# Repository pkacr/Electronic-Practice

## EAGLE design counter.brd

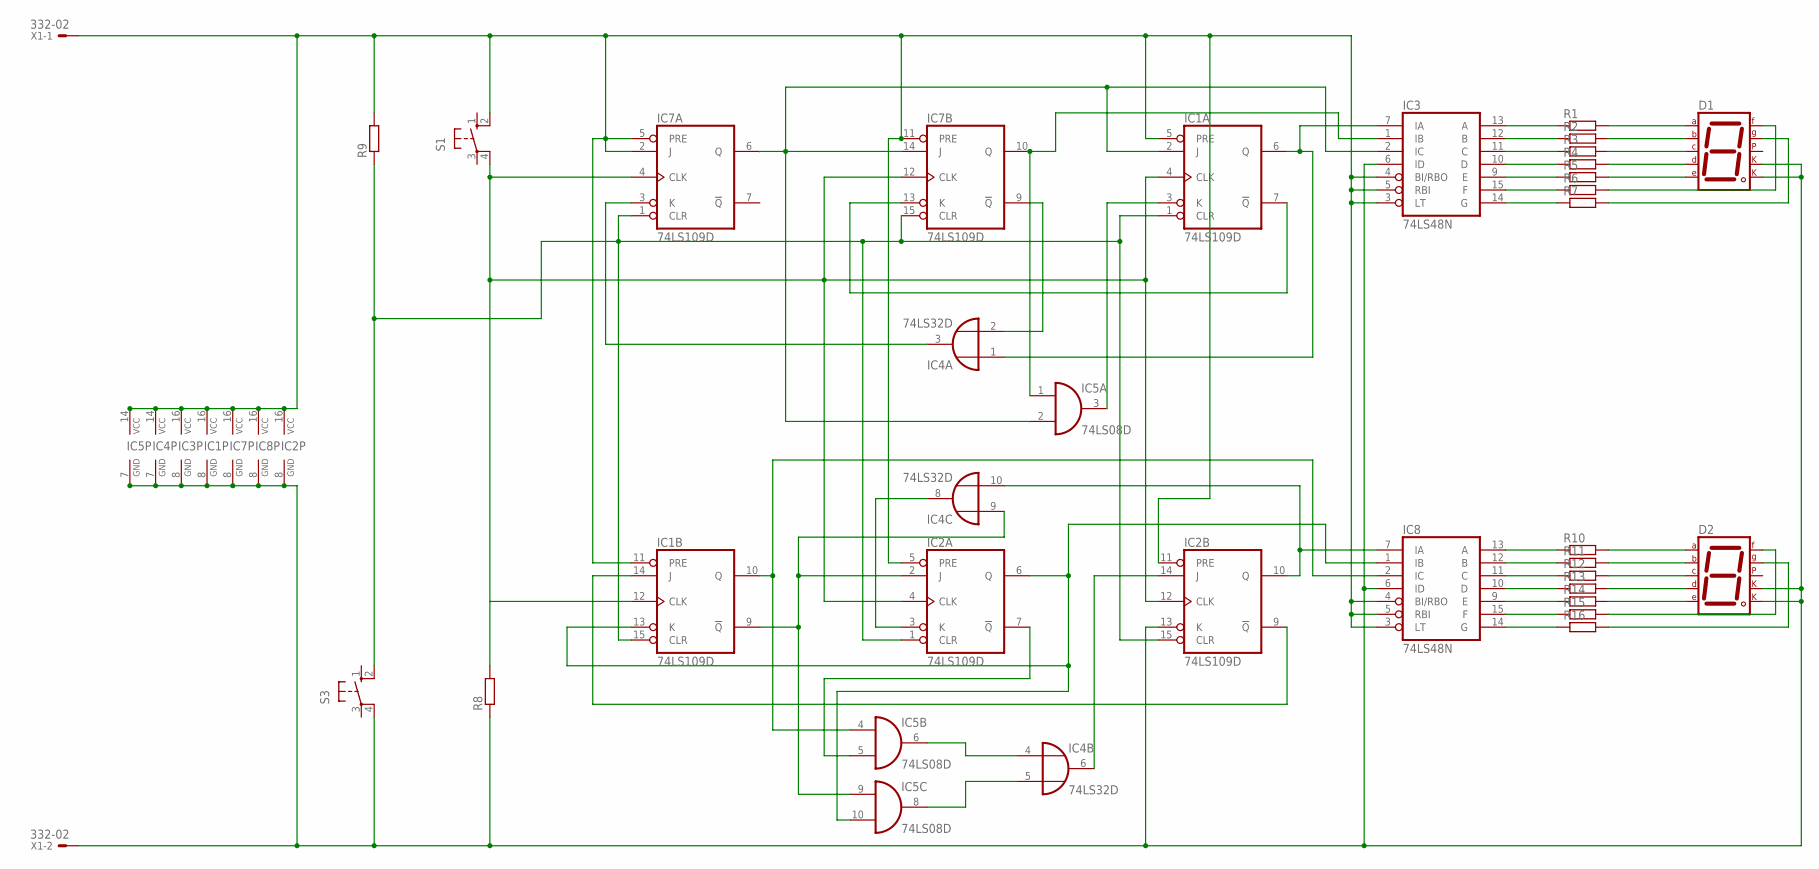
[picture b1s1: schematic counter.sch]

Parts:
D1, D2: 7SEG-CK; 7SEG-13
IC1, IC2, IC7: 74LS109D; SO16
IC3, IC8: 74LS48N; DIL16
IC4: 74LS32D; SO14
IC5: 74LS08D; SO14
R1, R2, R3, R4, R5, R6, R7, R8, R9, R10, R11, R12, R13, R14, R15, R16: R-EU_M0805; M0805
S1, S3: 10-XX; B3F-10XX
X1: 332-02

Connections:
unnamed: IC3.13 (A), R1.1
unnamed: D1.7 (A), R1.2
unnamed: IC3.12 (B), R2.1
unnamed: D1.6 (B), R2.2
unnamed: IC3.11 (C), R3.1
unnamed: D1.4 (C), R3.2
unnamed: IC3.10 (D), R4.1
unnamed: D1.2 (D), R4.2
unnamed: IC3.9 (E), R5.1
unnamed: D1.1 (E), R5.2
unnamed: IC3.15 (F), R6.1
unnamed: D1.9 (F), R6.2
unnamed: IC3.14 (G), R7.1
unnamed: D1.10 (G), R7.2
unnamed: IC1.4 (CLK), IC1.12 (CLK), IC2.4 (CLK), IC2.12 (CLK), IC7.4 (CLK), IC7.12 (CLK), R8.2, S1.4 (P1)
unnamed: IC1.2 (J), IC3.2 (IC), IC5.2 (I1), IC7.6 (Q), IC7.14 (J)
unnamed: IC1.1 (CLR), IC1.15 (CLR), IC2.1 (CLR), IC2.15 (CLR), IC7.1 (CLR), IC7.15 (CLR), R9.1, S3.2 (S1)
unnamed: IC4.3 (O), IC7.3 (K)
unnamed: IC1.7 (!Q), IC7.13 (K)
unnamed: IC3.1 (IB), IC5.1 (I0), IC7.10 (Q)
unnamed: IC2.10 (Q), IC4.10 (I1), IC8.7 (IA)
unnamed: IC1.3 (K), IC5.3 (O)
unnamed: IC1.14 (J), IC2.9 (!Q)
unnamed: IC4.2 (I1), IC7.9 (!Q)
unnamed: IC1.9 (!Q), IC2.2 (J), IC4.9 (I0), IC5.9 (I0)
unnamed: IC1.6 (Q), IC3.7 (IA), IC4.1 (I0)
unnamed: IC8.13 (A), R10.1
unnamed: IC2.14 (J), IC4.6 (O)
unnamed: D2.7 (A), R10.2
unnamed: IC8.12 (B), R11.1
unnamed: D2.6 (B), R11.2
unnamed: IC8.11 (C), R12.1
unnamed: D2.4 (C), R12.2
unnamed: IC8.10 (D), R13.1
unnamed: D2.2 (D), R13.2
unnamed: IC8.9 (E), R14.1
unnamed: D2.1 (E), R14.2
unnamed: IC8.15 (F), R15.1
unnamed: D2.9 (F), R15.2
unnamed: IC8.14 (G), R16.1
unnamed: D2.10 (G), R16.2
unnamed: IC1.5 (PRE), IC1.11 (PRE), IC1.16 (VCC), IC2.5 (PRE), IC2.11 (PRE), IC2.16 (VCC), IC3.3 (LT), IC3.4 (BI/RBO), IC3.5 (RBI), IC3.16 (VCC), IC4.14 (VCC), IC5.14 (VCC), IC7.2 (J), IC7.5 (PRE), IC7.11 (PRE), IC7.16 (VCC), IC8.3 (LT), IC8.4 (BI/RBO), IC8.5 (RBI), IC8.16 (VCC), R9.2, S1.2 (S1), X1.1
unnamed: D1.3 (CK1), D1.8 (CK2), D2.3 (CK1), D2.8 (CK2), IC1.8 (GND), IC2.8 (GND), IC2.13 (K), IC3.6 (ID), IC3.8 (GND), IC4.7 (GND), IC5.7 (GND), IC7.8 (GND), IC8.6 (ID), IC8.8 (GND), R8.1, S3.4 (P1), X1.2
unnamed: IC2.7 (!Q), IC5.5 (I1)
unnamed: IC4.4 (I0), IC5.6 (O)
unnamed: IC4.5 (I1), IC5.8 (O)
unnamed: IC1.10 (Q), IC5.4 (I0), IC8.2 (IC)
unnamed: IC2.3 (K), IC4.8 (O)
unnamed: IC1.13 (K), IC2.6 (Q), IC5.10 (I1), IC8.1 (IB)

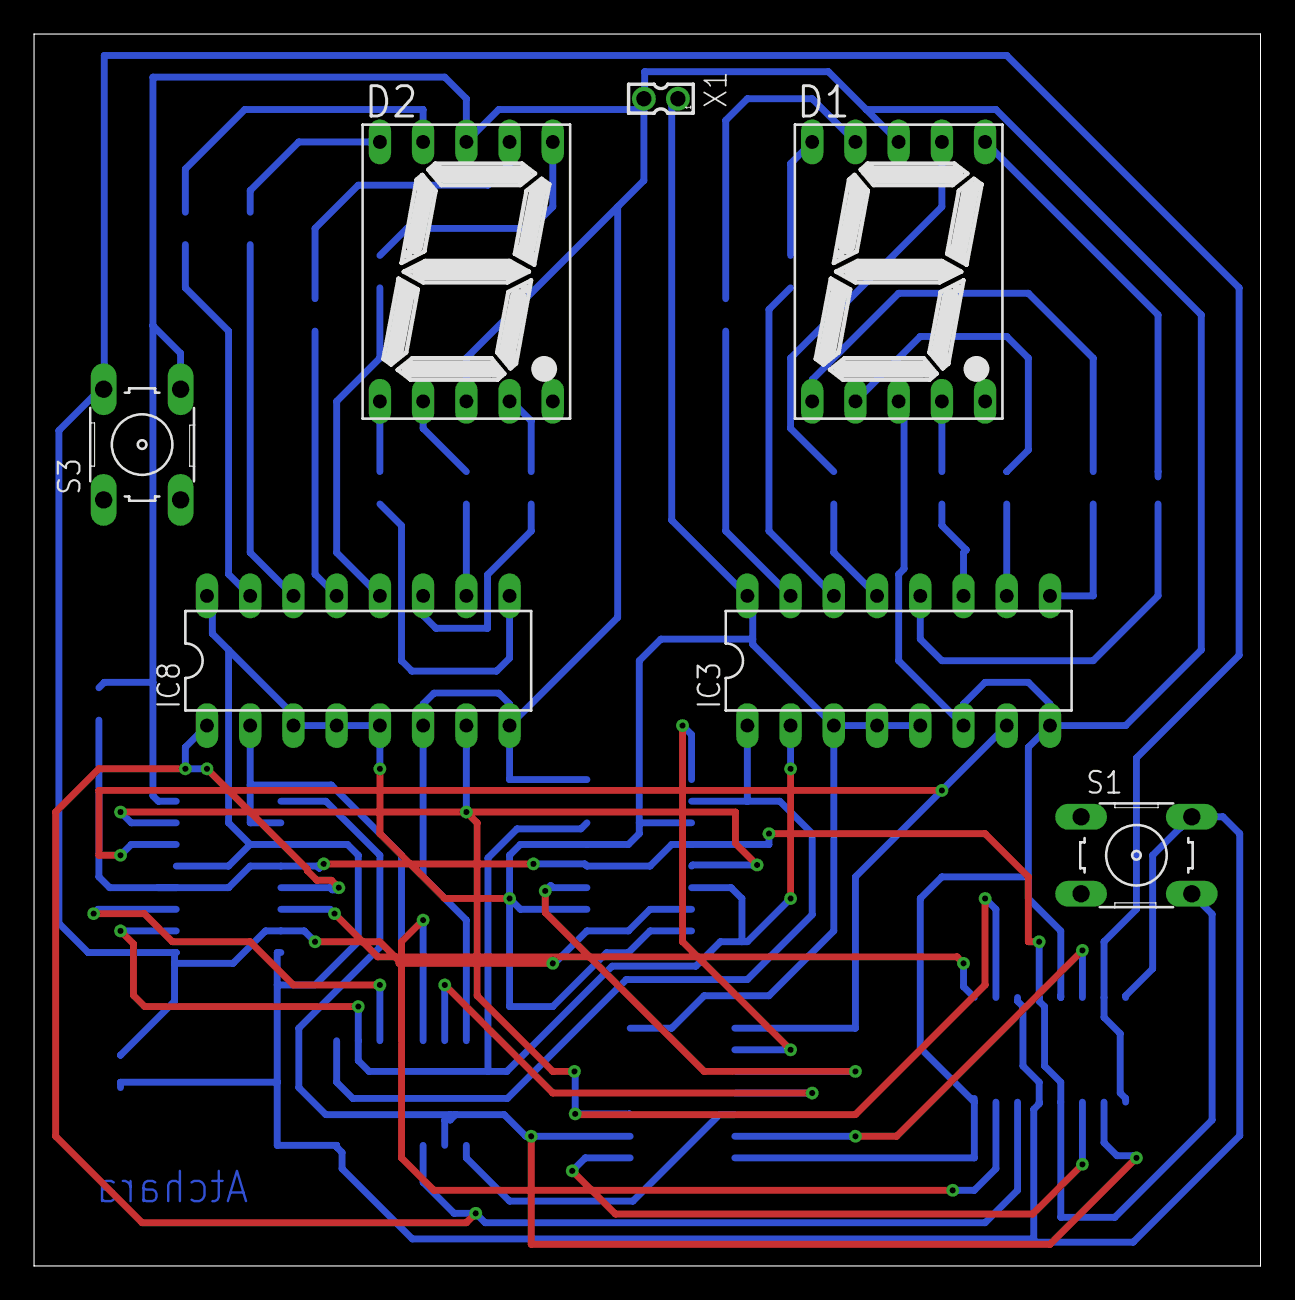
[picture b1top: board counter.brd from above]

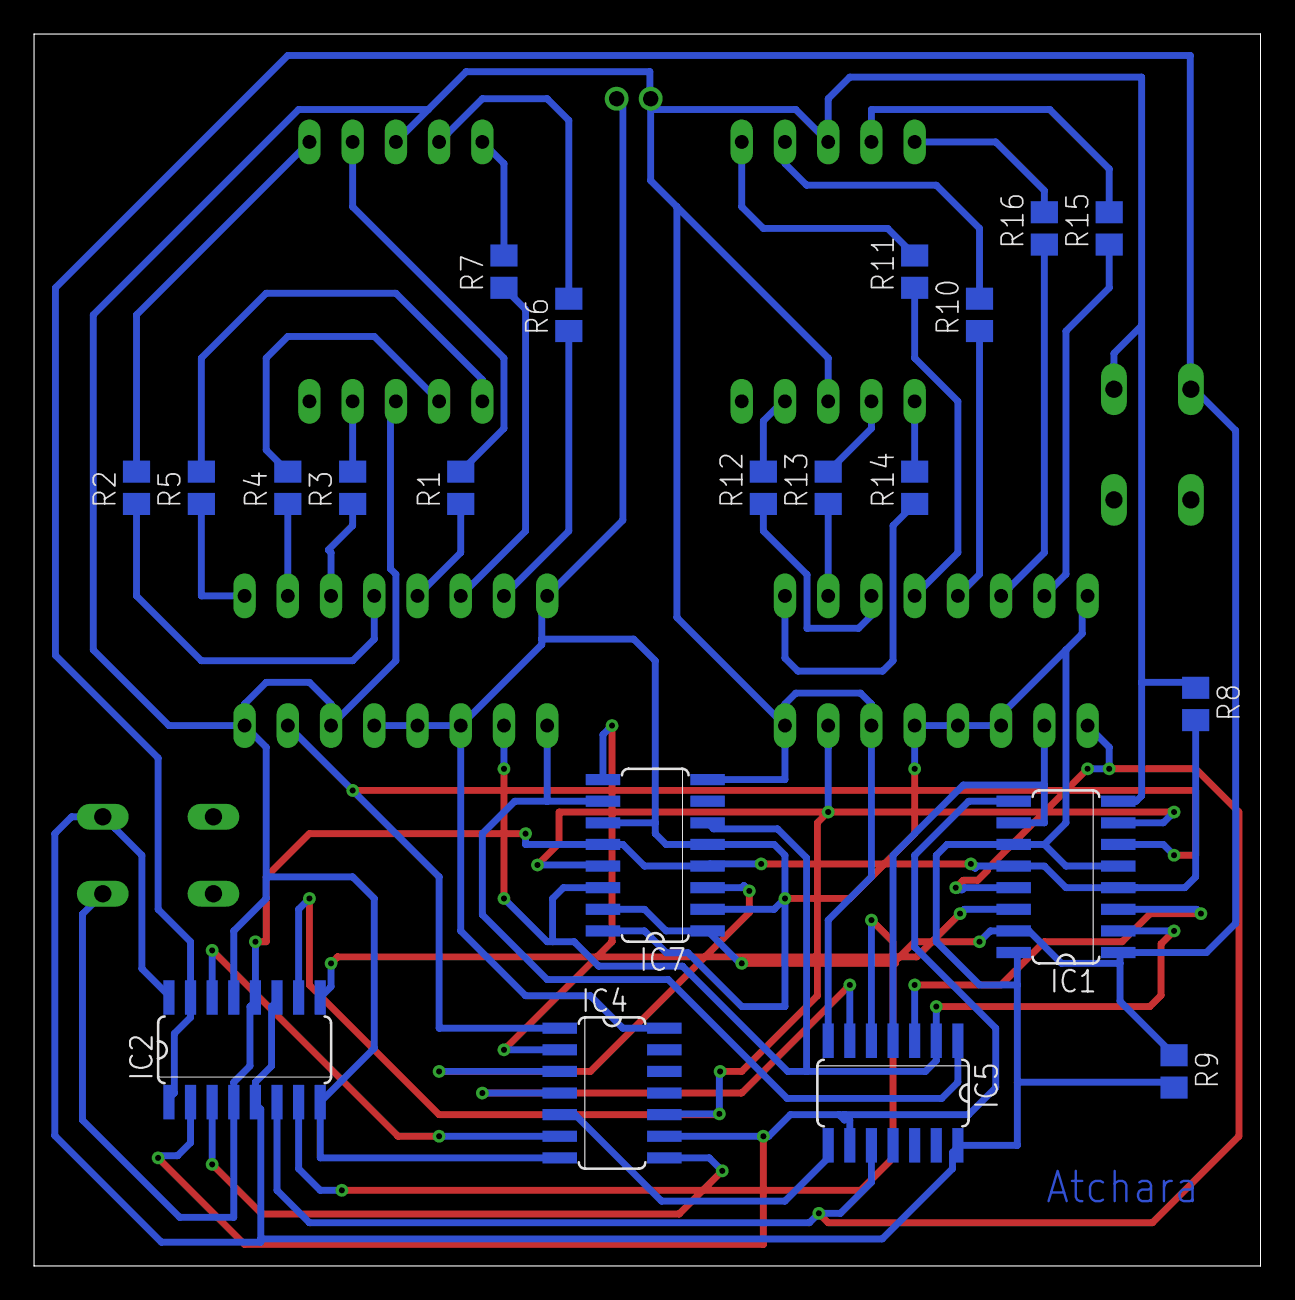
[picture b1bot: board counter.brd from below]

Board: 2 copper layers, 72.1 x 72.4 mm, 28 parts (21 on the bottom side), 49 nets.

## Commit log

2024-02-02 วงจรcounter
    นับเลข 64 47 15 26 73
